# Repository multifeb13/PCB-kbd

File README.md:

# Overview
Repository for PCB data of keyboards

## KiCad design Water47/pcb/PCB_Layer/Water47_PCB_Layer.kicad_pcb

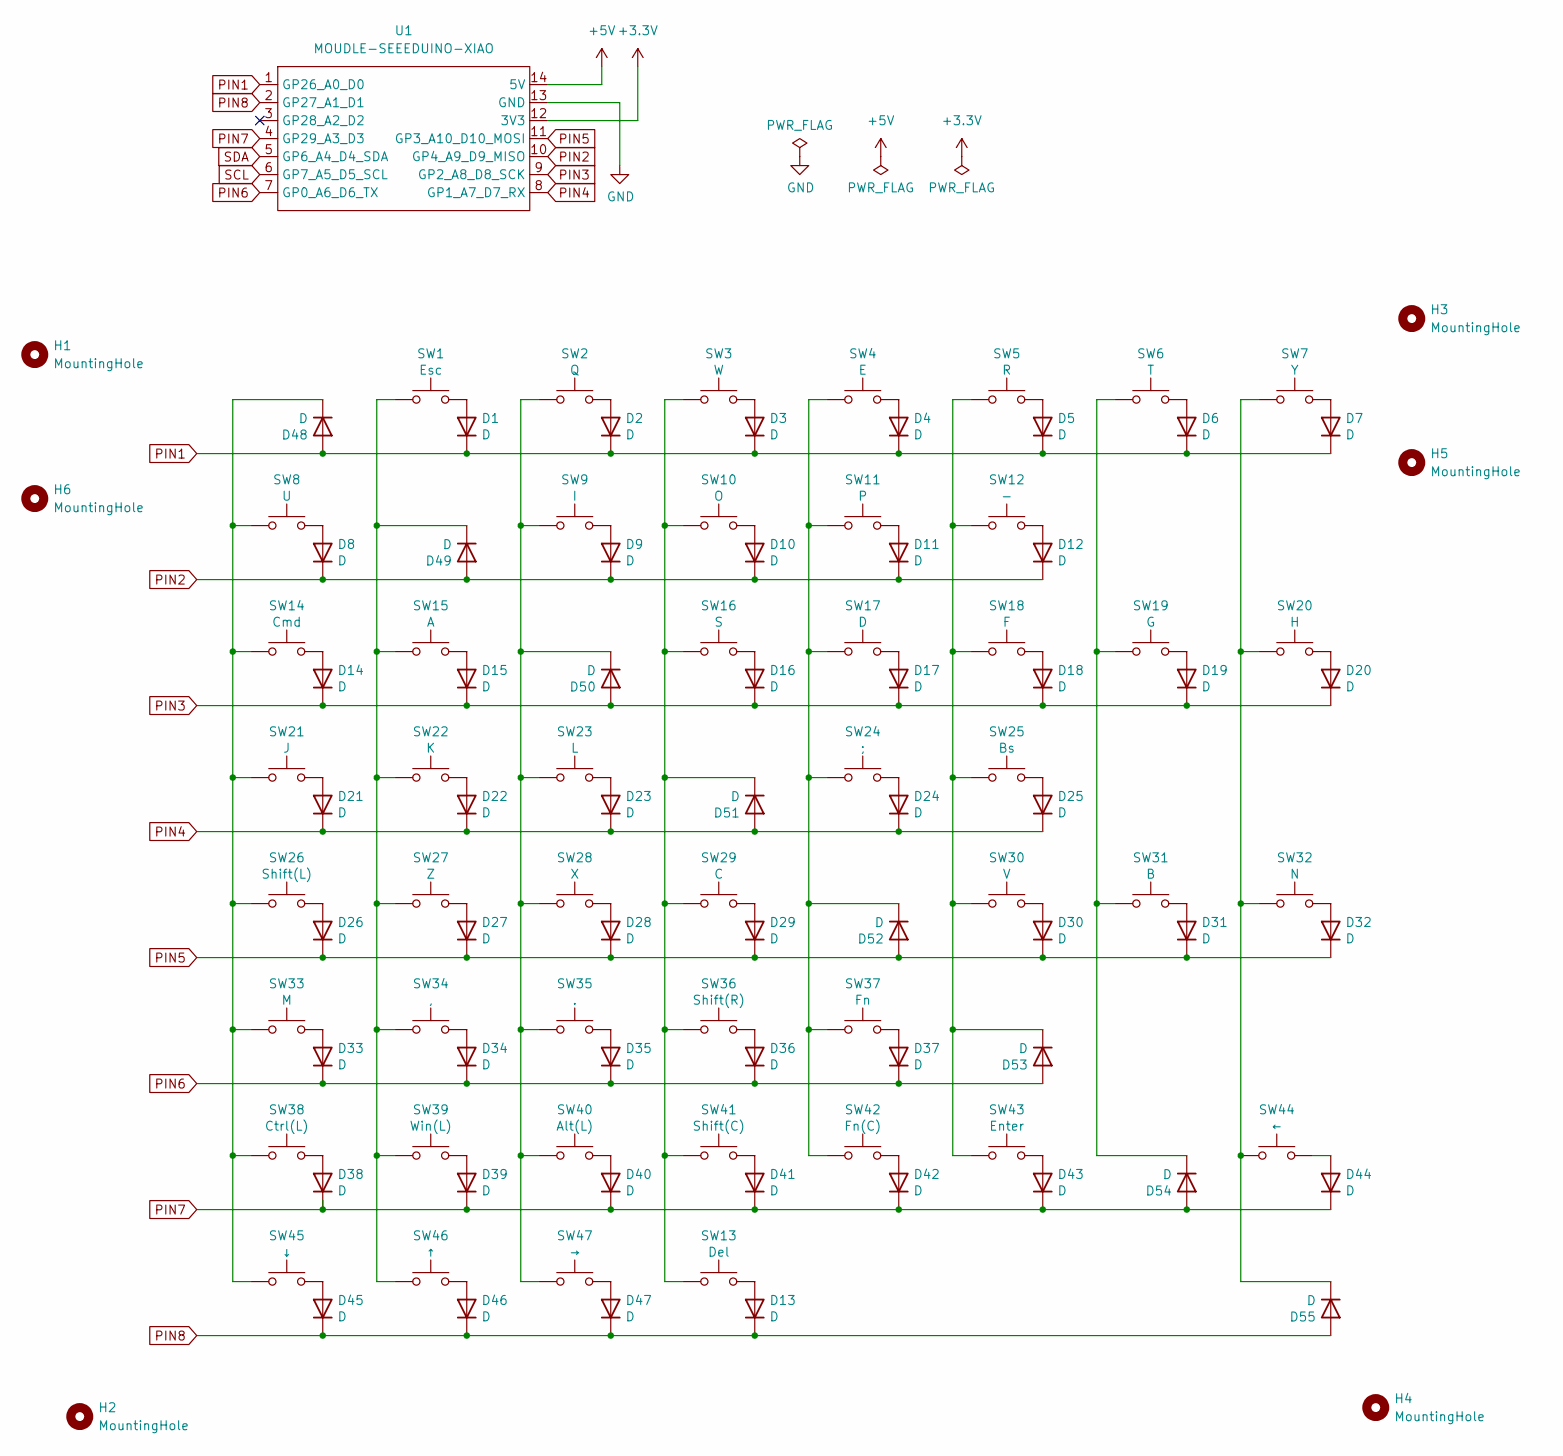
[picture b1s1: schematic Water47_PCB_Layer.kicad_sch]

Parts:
D1, D2, D3, D4, D5, D6, D7, D8, D9, D10, D11, D12, D13, D14, D15, D16, D17, D18, D19, D20, D21, D22, D23, D24, D25, D26, D27, D28, D29, D30, D31, D32, D33, D34, D35, D36, D37, D38, D39, D40, D41, D42, D43, D44, D45, D46, D47, D48, D49, D50, D51, D52, D53, D54, D55: D; Diode_SMD
H1, H2, H3, H4, H5, H6: MountingHole; m2_Spacer_Hole_hex
SW1: Esc; Kailh_Choc_V2_1u_wo_anker
SW2: Q; Kailh_Choc_V2_1u_wo_anker
SW3: W; Kailh_Choc_V2_1u_wo_anker
SW4: E; Kailh_Choc_V2_1u_wo_anker
SW5: R; Kailh_Choc_V2_1u_wo_anker
SW6: T; Kailh_Choc_V2_1u_wo_anker
SW7: Y; Kailh_Choc_V2_1u_wo_anker
SW8: U; Kailh_Choc_V2_1u_wo_anker
SW9: I; Kailh_Choc_V2_1u_wo_anker
SW10: O; Kailh_Choc_V2_1u_wo_anker
SW11: P; Kailh_Choc_V2_1u_wo_anker
SW12: -; Kailh_Choc_V2_1u_wo_anker
SW13: Del; Kailh_Choc_V2_1u_wo_anker
SW14: Cmd; Kailh_Choc_V2_1.25u_wo_anker
SW15: A; Kailh_Choc_V2_1u_wo_anker
SW16: S; Kailh_Choc_V2_1u_wo_anker
SW17: D; Kailh_Choc_V2_1u_wo_anker
SW18: F; Kailh_Choc_V2_1u_wo_anker
SW19: G; Kailh_Choc_V2_1u_wo_anker
SW20: H; Kailh_Choc_V2_1u_wo_anker
SW21: J; Kailh_Choc_V2_1u_wo_anker
SW22: K; Kailh_Choc_V2_1u_wo_anker
SW23: L; Kailh_Choc_V2_1u_wo_anker
SW24: ;; Kailh_Choc_V2_1u_wo_anker
SW25: Bs; Kailh_Choc_V2_1.75u_wo_anker
SW26: Shift(L); Kailh_Choc_V2_1.75u_wo_anker
SW27: Z; Kailh_Choc_V2_1u_wo_anker
SW28: X; Kailh_Choc_V2_1u_wo_anker
SW29: C; Kailh_Choc_V2_1u_wo_anker
SW30: V; Kailh_Choc_V2_1u_wo_anker
SW31: B; Kailh_Choc_V2_1u_wo_anker
SW32: N; Kailh_Choc_V2_1u_wo_anker
SW33: M; Kailh_Choc_V2_1u_wo_anker
SW34: ,; Kailh_Choc_V2_1u_wo_anker
SW35: .; Kailh_Choc_V2_1u_wo_anker
SW36: Shift(R); Kailh_Choc_V2_1.25u_wo_anker
SW37: Fn; Kailh_Choc_V2_1u_wo_anker
SW38: Ctrl(L); Kailh_Choc_V2_1.25u_wo_anker
SW39: Win(L); Kailh_Choc_V2_1.25u_wo_anker
SW40: Alt(L); Kailh_Choc_V2_1.5u_wo_anker
SW41: Shift(C); Kailh_Choc_V2_1.75u_wo_anker
SW42: Fn(C); Kailh_Choc_V2_1.25u_wo_anker
SW43: Enter; Kailh_Choc_V2_1.75u_wo_anker
SW44: ←; Kailh_Choc_V2_1.25u_wo_anker
SW45: ↓; Kailh_Choc_V2_1u_wo_anker
SW46: ↑; Kailh_Choc_V2_1u_wo_anker
SW47: →; Kailh_Choc_V2_1u_wo_anker
U1: MOUDLE-SEEEDUINO-XIAO; Micon_XIAO_TH

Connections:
+3.3V: U1.12 (3V3)
+5V: U1.14 (5V)
GND: U1.13 (GND)
unnamed: D1.2 (A), SW1.2
unnamed: D2.2 (A), SW2.2
unnamed: D3.2 (A), SW3.2
unnamed: D4.2 (A), SW4.2
unnamed: D5.2 (A), SW5.2
unnamed: D6.2 (A), SW6.2
unnamed: D7.2 (A), SW7.2
unnamed: D8.2 (A), SW8.2
unnamed: D9.2 (A), SW9.2
unnamed: D10.2 (A), SW10.2
unnamed: D11.2 (A), SW11.2
unnamed: D12.2 (A), SW12.2
unnamed: D13.2 (A), SW13.2
unnamed: D14.2 (A), SW14.2
unnamed: D15.2 (A), SW15.2
unnamed: D16.2 (A), SW16.2
unnamed: D17.2 (A), SW17.2
unnamed: D18.2 (A), SW18.2
unnamed: D19.2 (A), SW19.2
unnamed: D20.2 (A), SW20.2
unnamed: D21.2 (A), SW21.2
unnamed: D22.2 (A), SW22.2
unnamed: D23.2 (A), SW23.2
unnamed: D24.2 (A), SW24.2
unnamed: D25.2 (A), SW25.2
unnamed: D26.2 (A), SW26.2
unnamed: D27.2 (A), SW27.2
unnamed: D28.2 (A), SW28.2
unnamed: D29.2 (A), SW29.2
unnamed: D30.2 (A), SW30.2
unnamed: D31.2 (A), SW31.2
unnamed: D32.2 (A), SW32.2
unnamed: D33.2 (A), SW33.2
unnamed: D34.2 (A), SW34.2
unnamed: D35.2 (A), SW35.2
unnamed: D36.2 (A), SW36.2
unnamed: D37.2 (A), SW37.2
unnamed: D38.2 (A), SW38.2
unnamed: D39.2 (A), SW39.2
unnamed: D40.2 (A), SW40.2
unnamed: D41.2 (A), SW41.2
unnamed: D42.2 (A), SW42.2
unnamed: D43.2 (A), SW43.2
unnamed: D44.2 (A), SW44.2
unnamed: D45.2 (A), SW45.2
unnamed: D46.2 (A), SW46.2
unnamed: D47.2 (A), SW47.2
unnamed: D48.1 (K), SW8.1, SW14.1, SW21.1, SW26.1, SW33.1, SW38.1, SW45.1
unnamed: D49.1 (K), SW1.1, SW15.1, SW22.1, SW27.1, SW34.1, SW39.1, SW46.1
unnamed: D50.1 (K), SW2.1, SW9.1, SW23.1, SW28.1, SW35.1, SW40.1, SW47.1
unnamed: D51.1 (K), SW3.1, SW10.1, SW13.1, SW16.1, SW29.1, SW36.1, SW41.1
unnamed: D52.1 (K), SW4.1, SW11.1, SW17.1, SW24.1, SW37.1, SW42.1
unnamed: D53.1 (K), SW5.1, SW12.1, SW18.1, SW25.1, SW30.1, SW43.1
unnamed: D54.1 (K), SW6.1, SW19.1, SW31.1
unnamed: D55.1 (K), SW7.1, SW20.1, SW32.1, SW44.1
PIN1: D1.1 (K), D2.1 (K), D3.1 (K), D4.1 (K), D5.1 (K), D6.1 (K), D7.1 (K), D48.2 (A), U1.1 (GP26_A0_D0)
PIN2: D8.1 (K), D9.1 (K), D10.1 (K), D11.1 (K), D12.1 (K), D49.2 (A), U1.10 (GP4_A9_D9_MISO)
PIN3: D14.1 (K), D15.1 (K), D16.1 (K), D17.1 (K), D18.1 (K), D19.1 (K), D20.1 (K), D50.2 (A), U1.9 (GP2_A8_D8_SCK)
PIN4: D21.1 (K), D22.1 (K), D23.1 (K), D24.1 (K), D25.1 (K), D51.2 (A), U1.8 (GP1_A7_D7_RX)
PIN5: D26.1 (K), D27.1 (K), D28.1 (K), D29.1 (K), D30.1 (K), D31.1 (K), D32.1 (K), D52.2 (A), U1.11 (GP3_A10_D10_MOSI)
PIN6: D33.1 (K), D34.1 (K), D35.1 (K), D36.1 (K), D37.1 (K), D53.2 (A), U1.7 (GP0_A6_D6_TX)
PIN7: D38.1 (K), D39.1 (K), D40.1 (K), D41.1 (K), D42.1 (K), D43.1 (K), D44.1 (K), D54.2 (A), U1.4 (GP29_A3_D3)
PIN8: D13.1 (K), D45.1 (K), D46.1 (K), D47.1 (K), D55.2 (A), U1.2 (GP27_A1_D1)
SCL: U1.6 (GP7_A5_D5_SCL)
SDA: U1.5 (GP6_A4_D4_SDA)

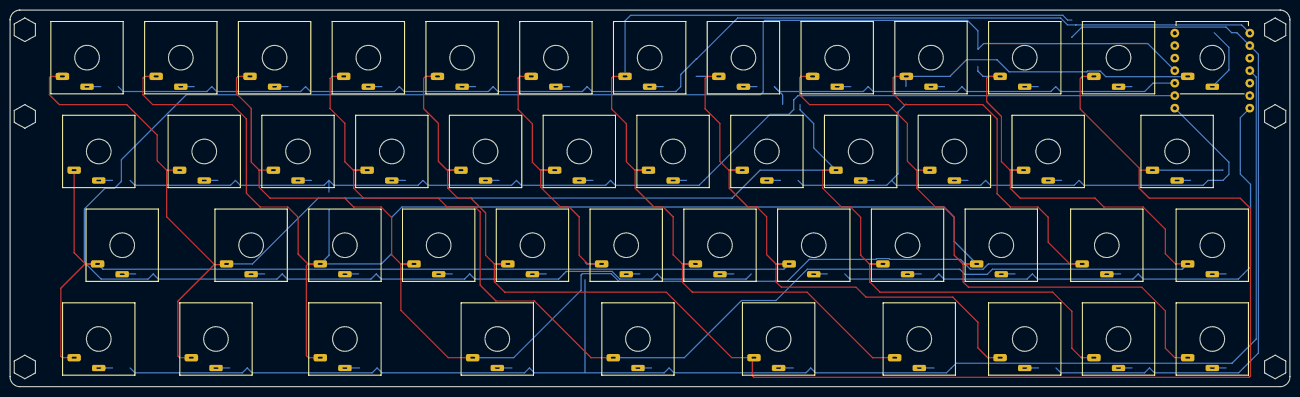
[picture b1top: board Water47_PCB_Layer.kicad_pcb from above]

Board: 2 copper layers, 260.0 x 76.5 mm, 109 parts (0 on the bottom side), 63 nets.

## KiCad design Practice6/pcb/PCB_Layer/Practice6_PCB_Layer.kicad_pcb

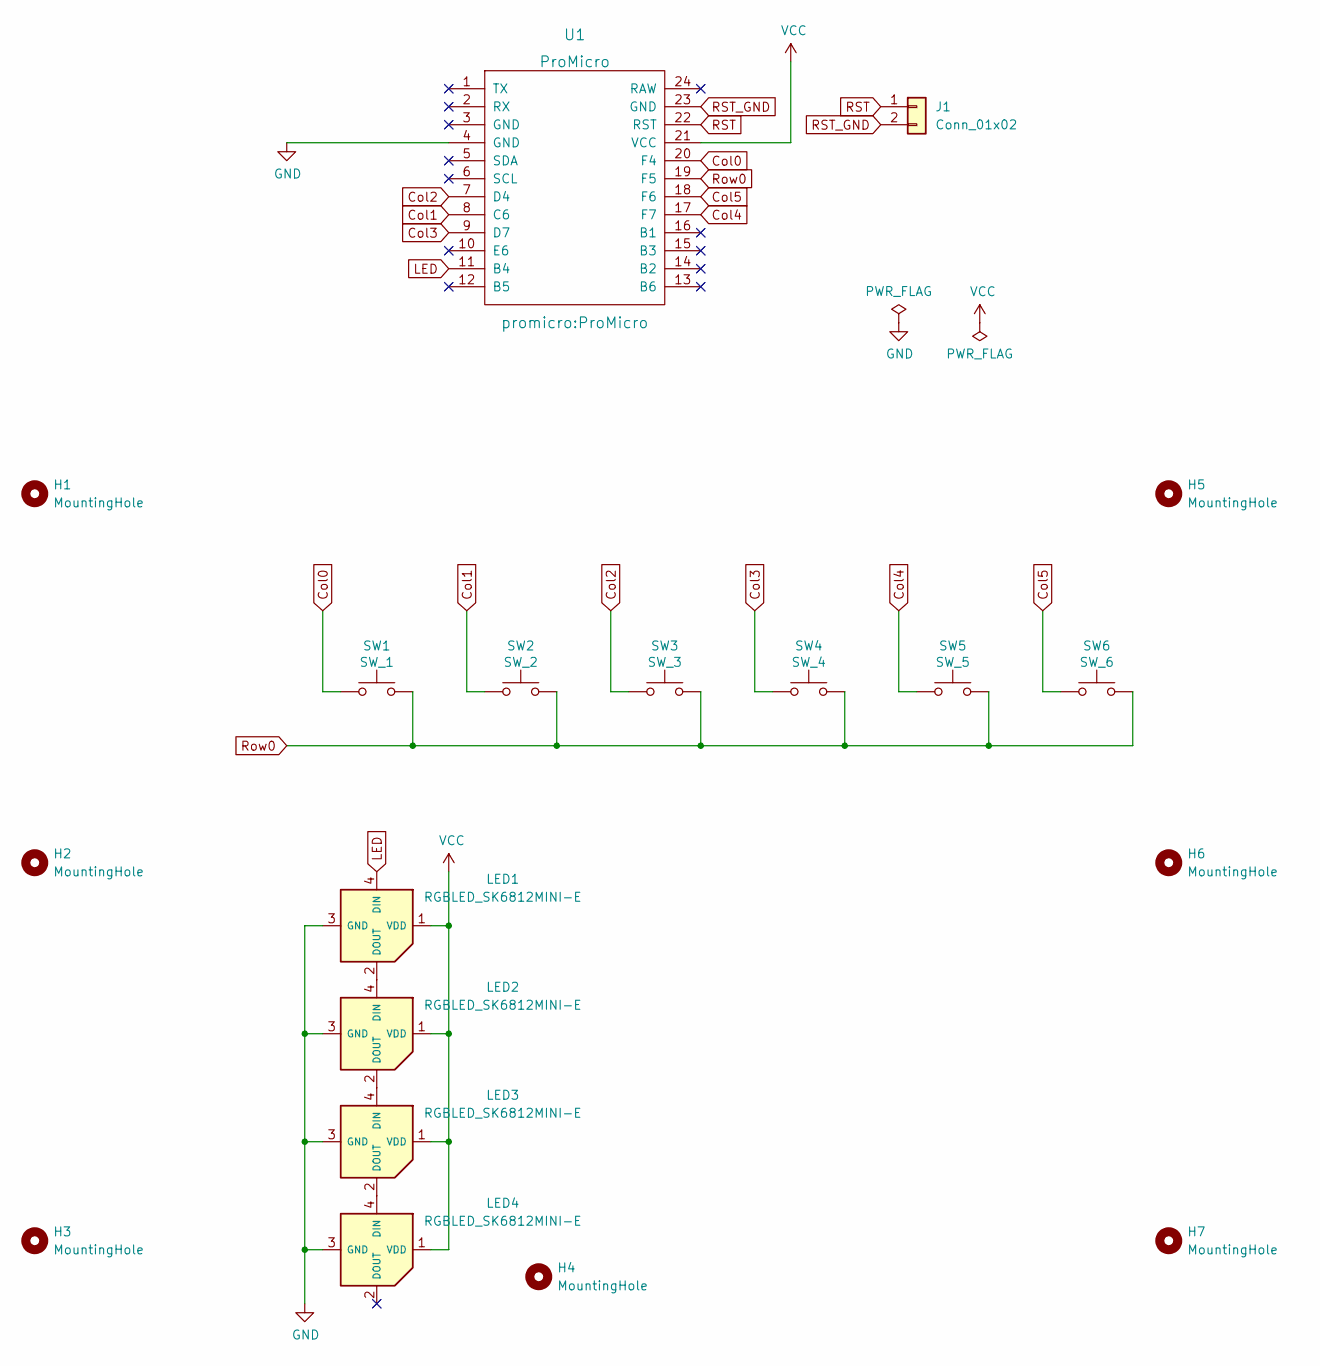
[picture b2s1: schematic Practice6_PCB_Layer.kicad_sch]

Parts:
H1, H2, H3, H4, H5, H6, H7: MountingHole; m2_Screw_Hole
J1: Conn_01x02; SW_108077_THDP07-060CB
LED1, LED2, LED3, LED4: RGBLED_SK6812MINI-E; LED_115478_SK6812MINI-E
SW1: SW_1; CherryMX_Solder_1u
SW2: SW_2; CherryMX_Solder_1u
SW3: SW_3; CherryMX_Solder_1u
SW4: SW_4; CherryMX_Solder_1u
SW5: SW_5; CherryMX_Solder_1u
SW6: SW_6; CherryMX_Solder_1u
U1: ProMicro

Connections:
Col0: SW1.1, U1.20 (F4)
Col1: SW2.1, U1.8 (C6)
Col2: SW3.1, U1.7 (D4)
Col3: SW4.1, U1.9 (D7)
Col4: SW5.1, U1.17 (F7)
Col5: SW6.1, U1.18 (F6)
GND: LED1.3 (GND), LED2.3 (GND), LED3.3 (GND), LED4.3 (GND), U1.4 (GND)
LED: LED1.4 (DIN), U1.11 (B4)
unnamed: LED1.2 (DOUT), LED2.4 (DIN)
unnamed: LED2.2 (DOUT), LED3.4 (DIN)
unnamed: LED3.2 (DOUT), LED4.4 (DIN)
RST: J1.1, U1.22 (RST)
RST_GND: J1.2, U1.23 (GND)
Row0: SW1.2, SW2.2, SW3.2, SW4.2, SW5.2, SW6.2, U1.19 (F5)
VCC: LED1.1 (VDD), LED2.1 (VDD), LED3.1 (VDD), LED4.1 (VDD), U1.21 (VCC)

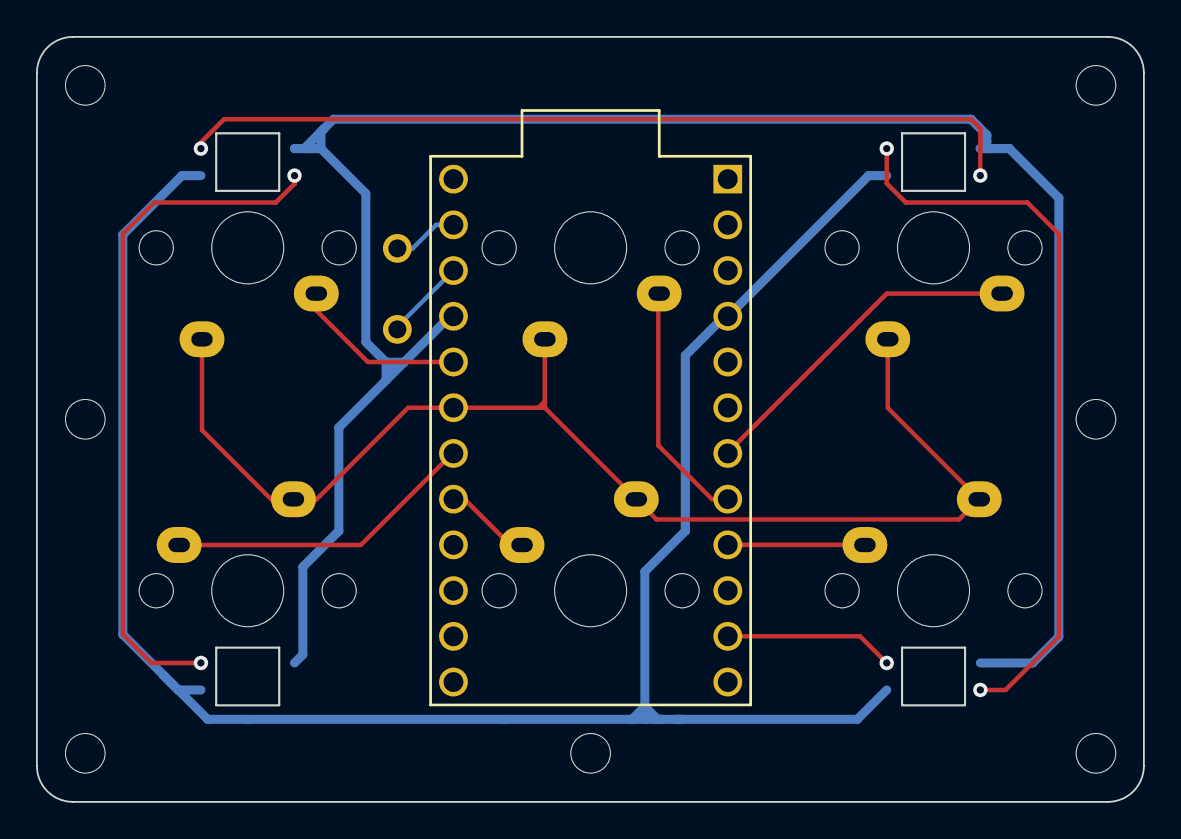
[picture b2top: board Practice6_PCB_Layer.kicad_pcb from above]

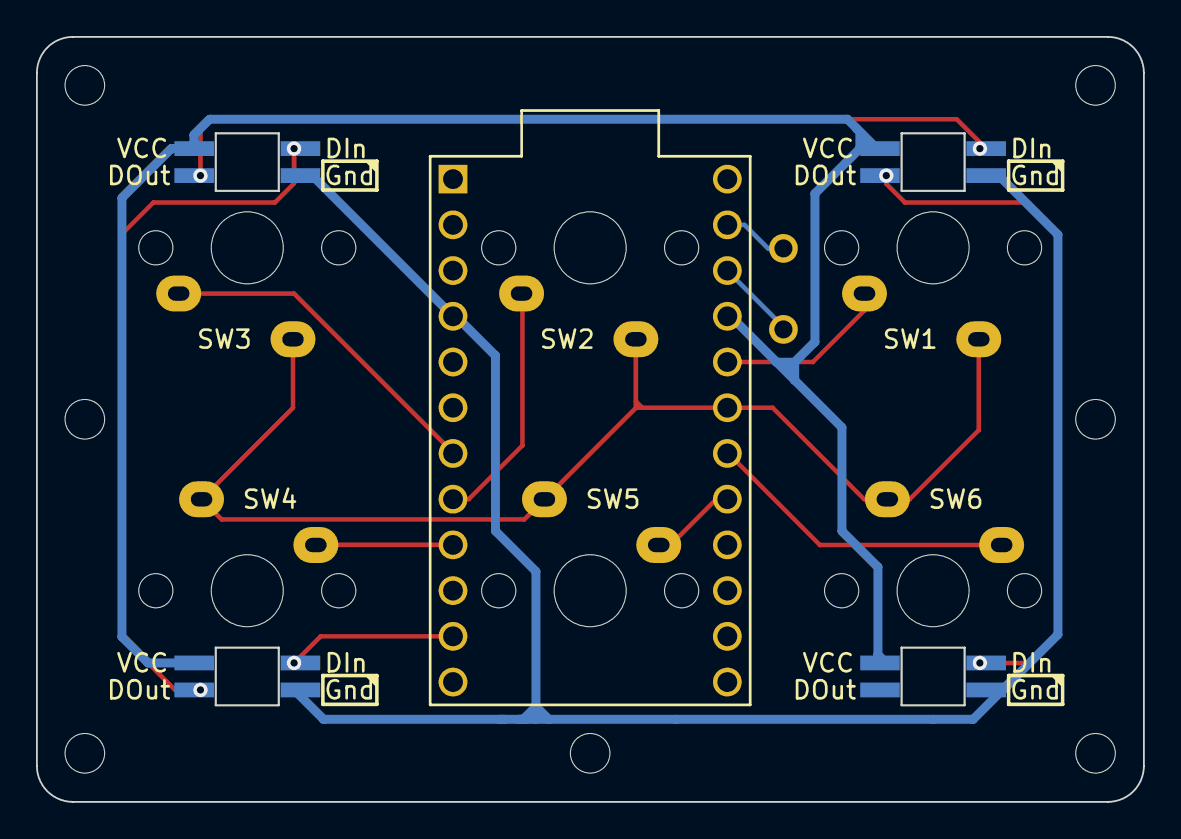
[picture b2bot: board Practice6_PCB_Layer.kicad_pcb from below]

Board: 2 copper layers, 61.5 x 42.5 mm, 19 parts (6 on the bottom side), 15 nets.

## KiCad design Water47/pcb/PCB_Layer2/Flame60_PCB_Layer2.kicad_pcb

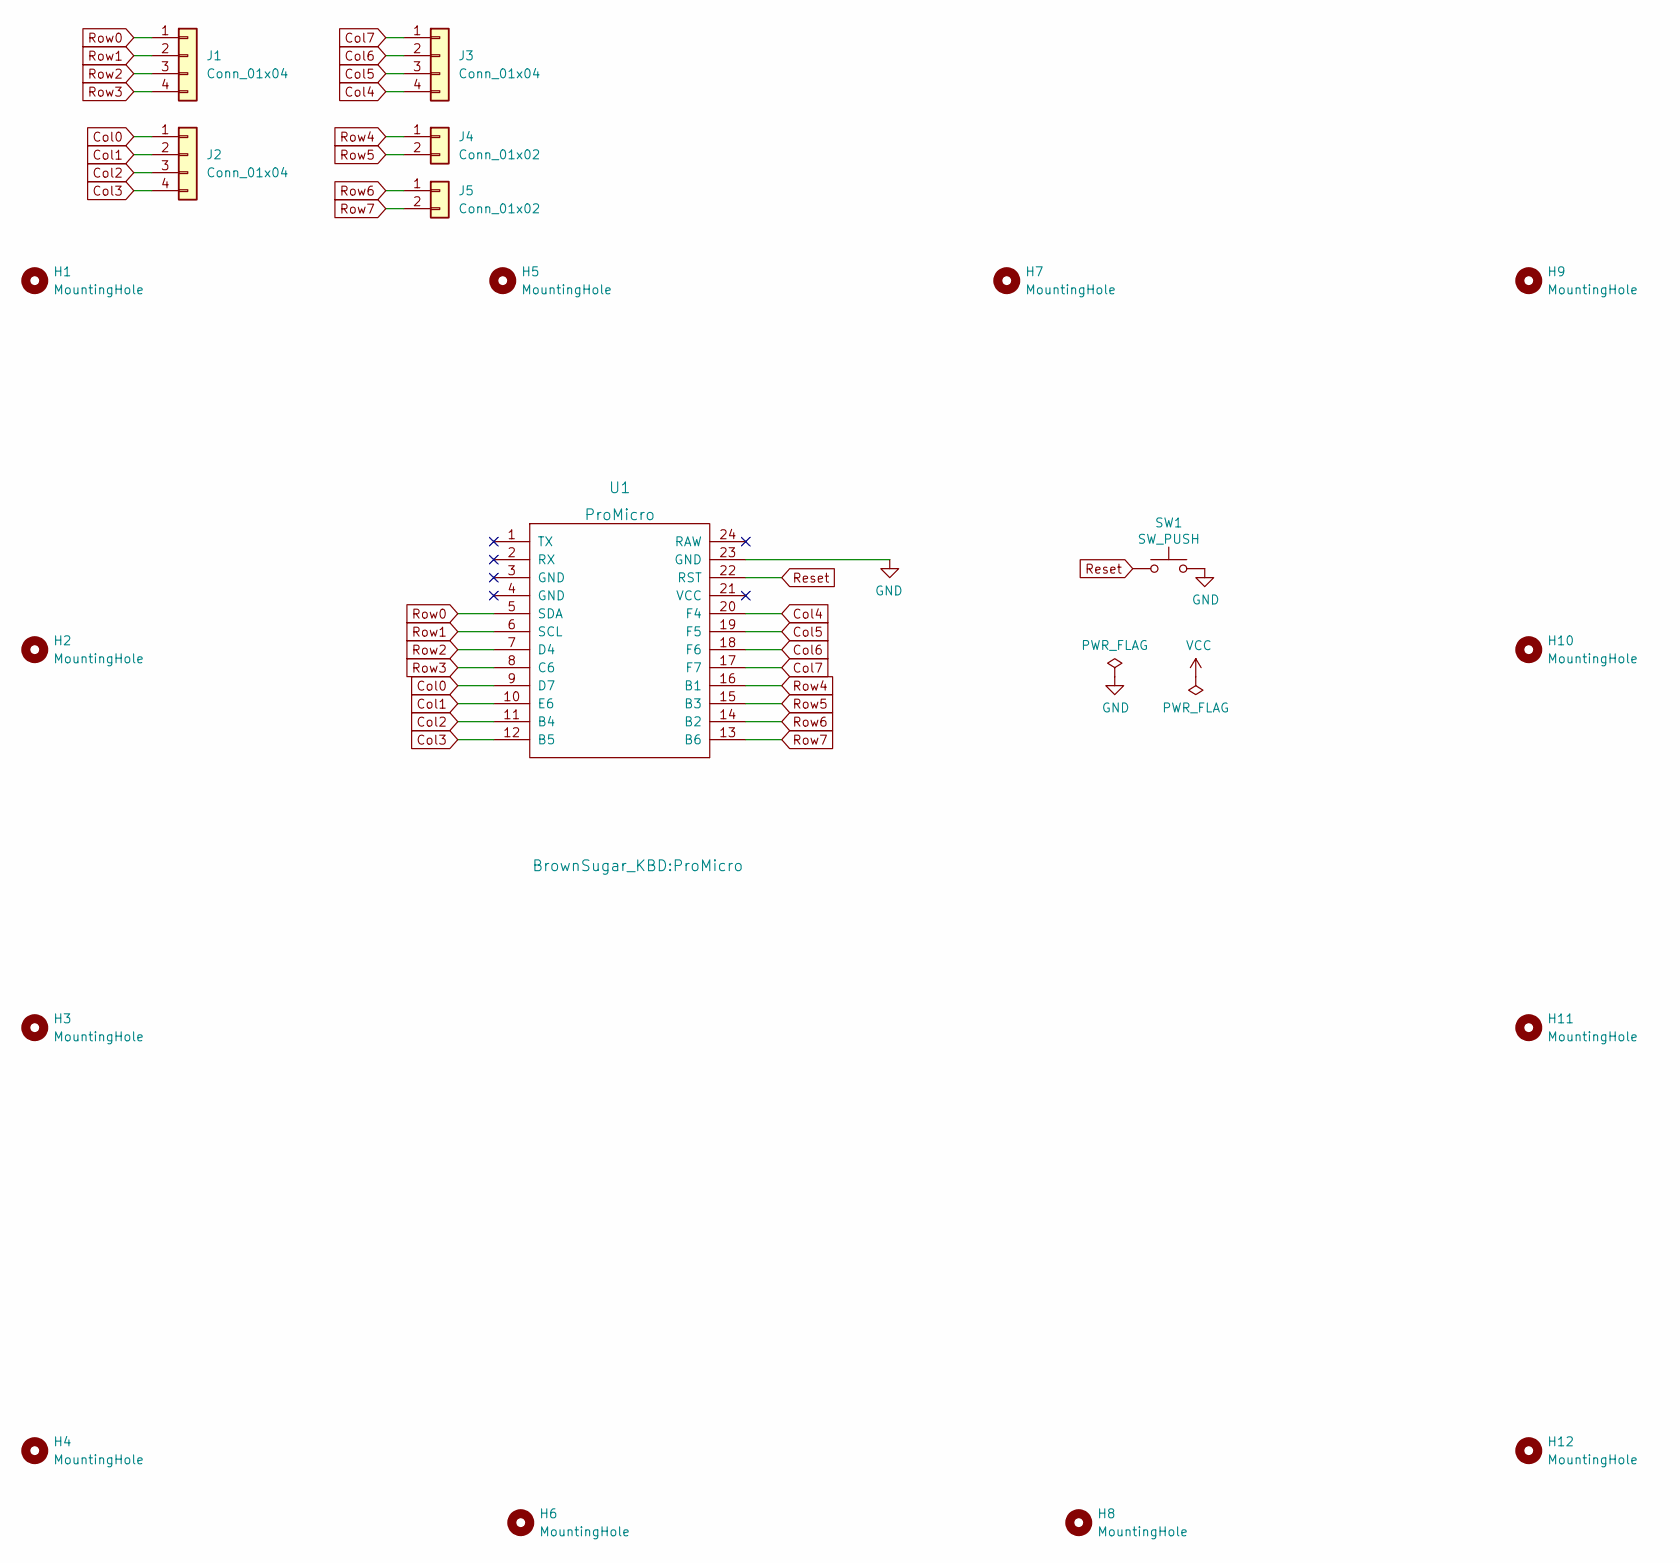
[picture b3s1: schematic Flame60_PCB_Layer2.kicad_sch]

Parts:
H1, H2, H3, H4, H5, H6, H7, H8, H9, H10, H11, H12: MountingHole; m2_Screw_Hole
J1, J2, J3: Conn_01x04; PinSocket_1x04_P2.54mm_Vertical
J4, J5: Conn_01x02; PinSocket_1x02_P2.54mm_Vertical
SW1: SW_PUSH; SW_107193_SKHHLPA010
U1: ProMicro

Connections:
Col0: J2.1, U1.9 (D7)
Col1: J2.2, U1.10 (E6)
Col2: J2.3, U1.11 (B4)
Col3: J2.4, U1.12 (B5)
Col4: J3.4, U1.20 (F4)
Col5: J3.3, U1.19 (F5)
Col6: J3.2, U1.18 (F6)
Col7: J3.1, U1.17 (F7)
GND: SW1.2, U1.23 (GND)
Reset: SW1.1, U1.22 (RST)
Row0: J1.1, U1.5 (SDA)
Row1: J1.2, U1.6 (SCL)
Row2: J1.3, U1.7 (D4)
Row3: J1.4, U1.8 (C6)
Row4: J4.1, U1.16 (B1)
Row5: J4.2, U1.15 (B3)
Row6: J5.1, U1.14 (B2)
Row7: J5.2, U1.13 (B6)

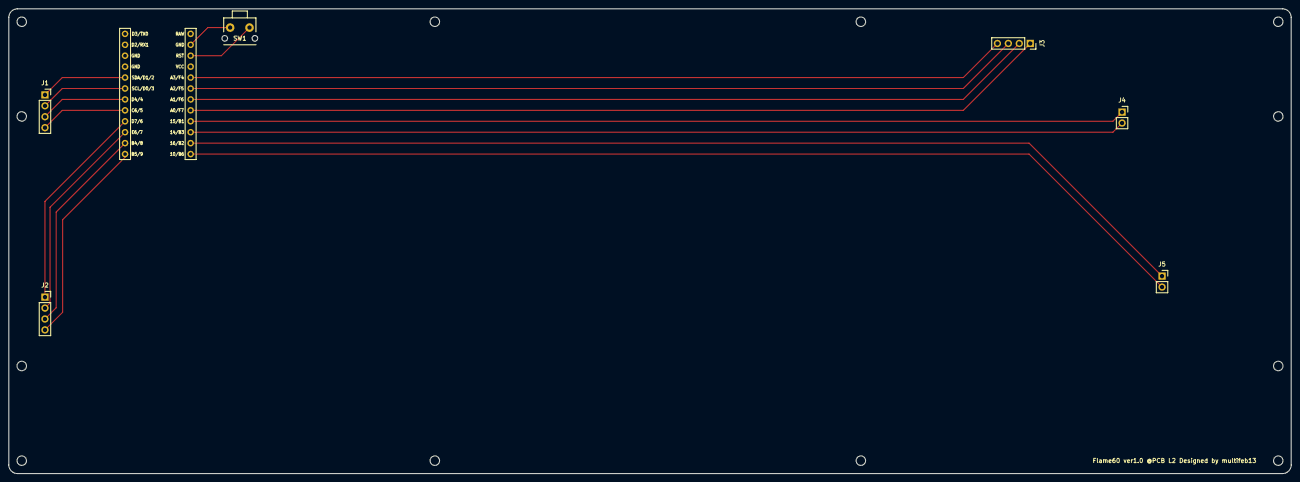
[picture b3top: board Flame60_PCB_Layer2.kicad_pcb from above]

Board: 2 copper layers, 298.0 x 108.0 mm, 19 parts (0 on the bottom side), 18 nets.

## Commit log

2024-11-26 add: Flame60 ver1.0
2024-12-15 add: Land1 ver 1.0
2024-12-15 fix: remove redundant wires
2024-12-15 feat: consistency of wiring
2024-12-15 add: Hurricane6 ver1.0
2024-12-23 feat: wiring
    - consistency of wiring
    - remove redundant wiring for GND(pin 3, 23)
2024-12-24 featr: add reset switch and modify wiring
2024-12-24 feat: remove logo silk
2024-12-24 fix: silk text and Y position
2025-01-05 add: Water47(kle data)
2025-01-05 add: Water47(PCB data)
2025-01-05 feat: change PCB size(vertical)
2025-01-12 feat: first wiring
2025-01-12 fix: wiring
    - wiring for SW pin 1
    - unconnected wire warning
2025-01-13 fix: clearance between footprint and wire
2025-01-13 feat: add silkscreen of MCU
2025-01-13 fix: corner wiring
2025-01-13 fix: silkscreen position
2025-01-13 feat: add symbol, annotating
    add MoutingHoles
    update annotating
2025-01-13 feat: remove unnecessary PCB
2025-01-13 add: Top board PCB
2025-01-13 feat: change key layout
    2u -> 1.75u to not put stabilizer
2025-01-13 fix: rename Top layer file name
2025-01-18 feat: change micon direction
2025-01-19 feat: add bottom board layout size
2025-01-19 feat: change mounting spacer to hex
2025-01-20 feat: change mounting hole
    PCB : Hex
    Others : Round
2025-01-20 feat: ignore reference micon parts
2025-01-20 feat: add mounting holes
2025-01-22 feat: add logo
2025-01-22 fix: footprint rotation
2025-01-23 fix: clearance between diode and PCB edge
2025-01-23 feat: increase logo size
2025-01-23 feat: add mounting hole, set gerber path
2025-01-23 feat: ignore gerber path
2025-01-23 fix: mounting hole rotation
2025-01-23 feat: remove unused micon footprint
2025-01-23 feat: add logo on Top
2025-01-25 add: fork Practice6 from Hurricane6
2025-01-25 feat: remove silkscreen
2025-01-25 fix: board size dimension
2025-01-26 feat: set gerber path
2025-01-26 fix: RST switch parts, hole position
2025-02-11 feat: change micon pin name
2025-02-11 fix: invisible redundant silkscreen
2025-05-05 add: docs
